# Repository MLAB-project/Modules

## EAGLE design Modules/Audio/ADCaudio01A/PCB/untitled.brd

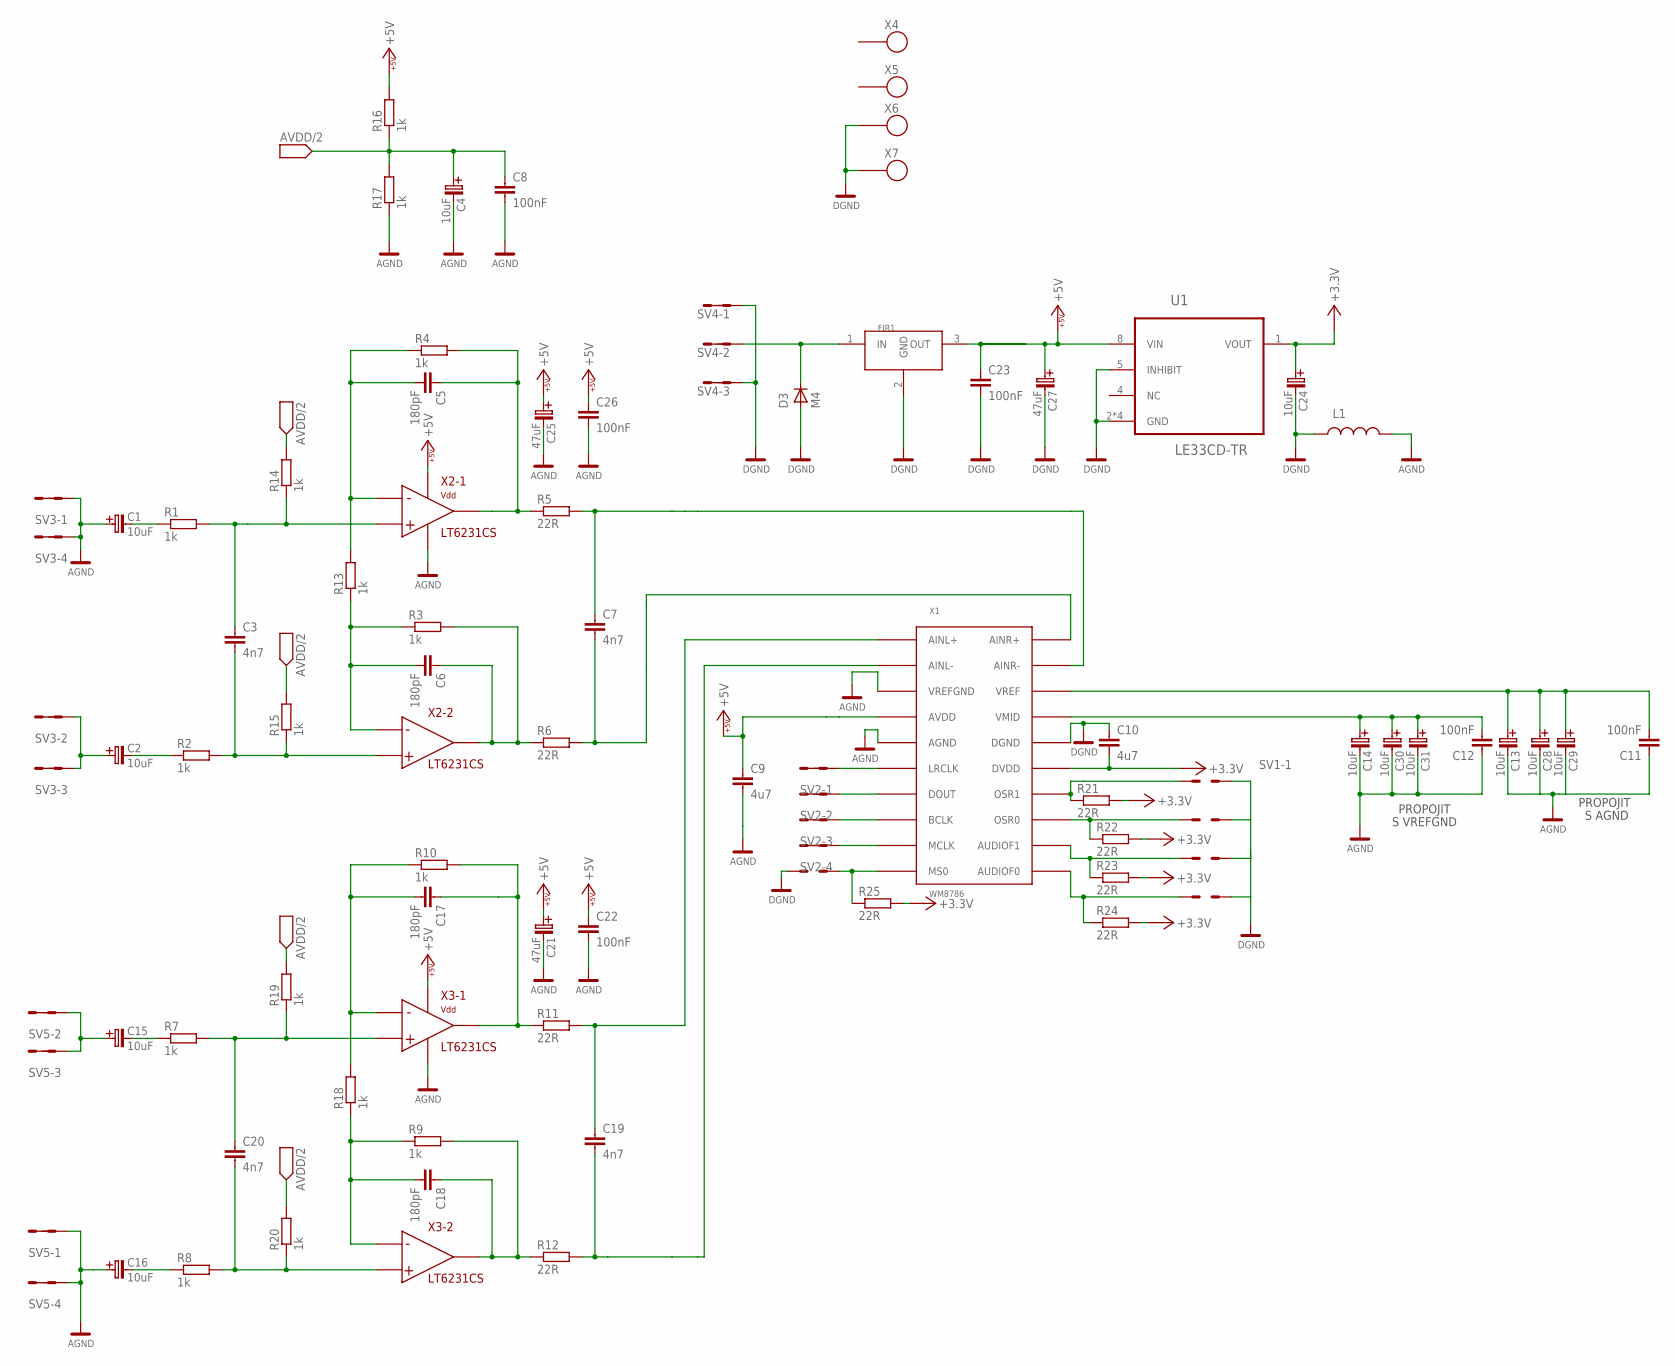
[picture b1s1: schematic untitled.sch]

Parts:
C1, C2, C4, C13, C14, C15, C16, C24, C28, C29, C30, C31: 10uF; B
C3, C7, C19, C20: 4n7; C0805
C5, C6, C17, C18: 180pF; C0805
C8, C11, C12, C22, C23, C26: 100nF; C0805
C9, C10: 4u7; C0805
C21, C25, C27: 47uF; B
D3: M4; SMA
FIR1: FILTR0805; F0805
L1: L0805
R1, R2, R3, R4, R7, R8, R9, R10, R13, R14, R15, R16, R17, R18, R19, R20: 1k; 0805
R5, R6, R11, R12, R21, R22, R23, R24, R25: 22R; 0805
SV1: MA05-3; MA05-2
SV2, SV3, SV5: MA04-2
SV4: MA03-2
U1: LE33CD-TR; SOIC127P600X175-8N
X1: WM8786; SSOP20
X2, X3: LT6231CS; SO8
X4, X5, X6, X7: SROUB3M

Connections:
1: C20.1, R7.2, R19.1, X3.3 (+)
4: C3.1, R1.2, R14.1, X2.3 (+)
+3.3V: C10.2, C24.+ (C_EL+), R21.2, R22.2, R23.2, R24.2, R25.2, U1.1 (VOUT), X1.15 (DVDD)
+5V: C9.1, C21.+ (C_EL+), C22.1, C23.1, C25.+ (C_EL+), C26.1, C27.+ (C_EL+), FIR1.3 (OUT), R16.2, U1.8 (VIN), X1.4 (AVDD), X2.8 (VDD), X3.8 (VDD)
AGND: C1.+ (C_EL+), C4.- (C_EL-), C8.2, C9.2, C11.1, C12.1, C13.- (C_EL-), C14.- (C_EL-), C16.+ (C_EL+), C21.- (C_EL-), C22.2, C25.- (C_EL-), C26.2, C28.- (C_EL-), C29.- (C_EL-), C30.- (C_EL-), C31.- (C_EL-), L1.2, R17.1, SV3.1, SV3.2, SV3.7, SV3.8, SV5.1, SV5.2, SV5.7, SV5.8, X1.3 (VREFGND), X1.5 (AGND), X2.4 (GND), X3.4 (GND)
AVDD/2: C4.+ (C_EL+), C8.1, R14.2, R15.2, R16.1, R17.2, R19.2, R20.2
DGND: C10.1, C23.2, C24.- (C_EL-), C27.- (C_EL-), D3.A, FIR1.2 (GND), L1.1, SV1.1, SV1.3, SV1.5, SV1.7, SV1.9, SV4.1, SV4.2, SV4.5, SV4.6, U1.2 (GND), U1.3 (GND), U1.5 (INHIBIT), U1.6 (GND), U1.7 (GND), X1.16 (DGND), X6.P$1, X7.P$1
unnamed: C5.2, R4.1, R13.2, X2.2 (-)
unnamed: C1.- (C_EL-), R1.1
unnamed: R21.1, SV1.8, X1.14 (OSR1)
unnamed: C6.2, R3.1, R13.1, X2.6 (-)
unnamed: C2.- (C_EL-), R2.1
unnamed: C6.1, R3.2, R6.1, X2.7 (VOUT)
unnamed: C7.1, R5.2, X1.19 (AINR-)
unnamed: R23.1, SV1.4, X1.12 (AUDIOF1)
unnamed: C17.2, R10.1, R18.2, X3.2 (-)
unnamed: C15.- (C_EL-), R7.1
unnamed: C18.2, R9.1, R18.1, X3.6 (-)
unnamed: C16.- (C_EL-), R8.1
unnamed: C18.1, R9.2, R12.1, X3.7 (VOUT)
unnamed: C19.1, R11.2, X1.1 (AINL+)
unnamed: R24.1, SV1.2, X1.11 (AUDIOF0)
unnamed: C15.+ (C_EL+), SV5.3, SV5.4, SV5.5, SV5.6
unnamed: C20.2, R8.2, R20.1, X3.5 (+)
unnamed: C2.+ (C_EL+), SV3.3, SV3.4, SV3.5, SV3.6
unnamed: R22.1, SV1.6, X1.13 (OSR0)
unnamed: C19.2, R12.2, X1.2 (AINL-)
unnamed: C12.2, C14.+ (C_EL+), C30.+ (C_EL+), C31.+ (C_EL+), X1.17 (VMID)
unnamed: C11.2, C13.+ (C_EL+), C28.+ (C_EL+), C29.+ (C_EL+), X1.18 (VREF)
unnamed: R25.1, SV1.10, X1.10 (MS0)
unnamed: SV2.1, SV2.2, X1.6 (LRCLK)
unnamed: SV2.3, SV2.4, X1.7 (DOUT)
unnamed: SV2.5, SV2.6, X1.8 (BCLK)
unnamed: SV2.7, SV2.8, X1.9 (MCLK)
unnamed: C3.2, R2.2, R15.1, X2.5 (+)
unnamed: C5.1, R4.2, R5.1, X2.1 (VOUT)
unnamed: C17.1, R10.2, R11.1, X3.1 (VOUT)
unnamed: C7.2, R6.2, X1.20 (AINR+)
unnamed: D3.K (C), FIR1.1 (IN), SV4.3, SV4.4

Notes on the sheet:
PROPOJIT
S VREFGND
S AGND

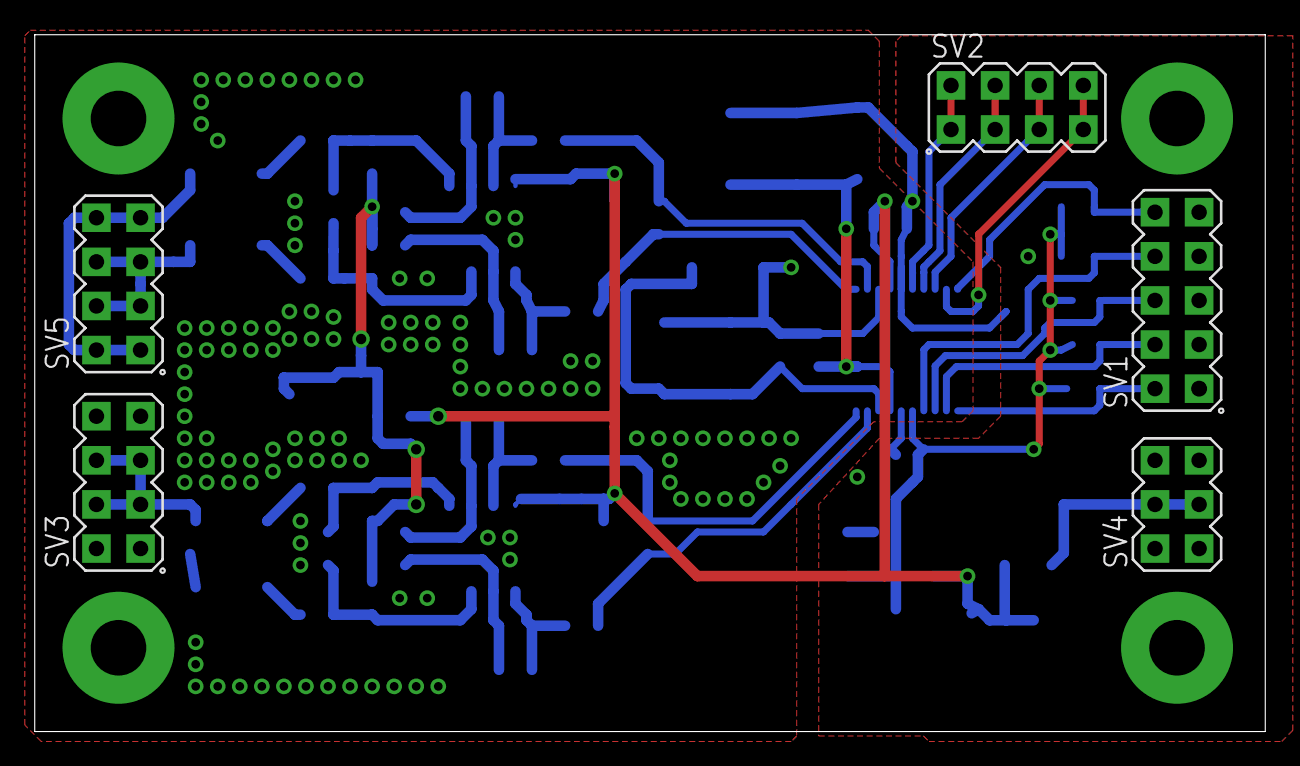
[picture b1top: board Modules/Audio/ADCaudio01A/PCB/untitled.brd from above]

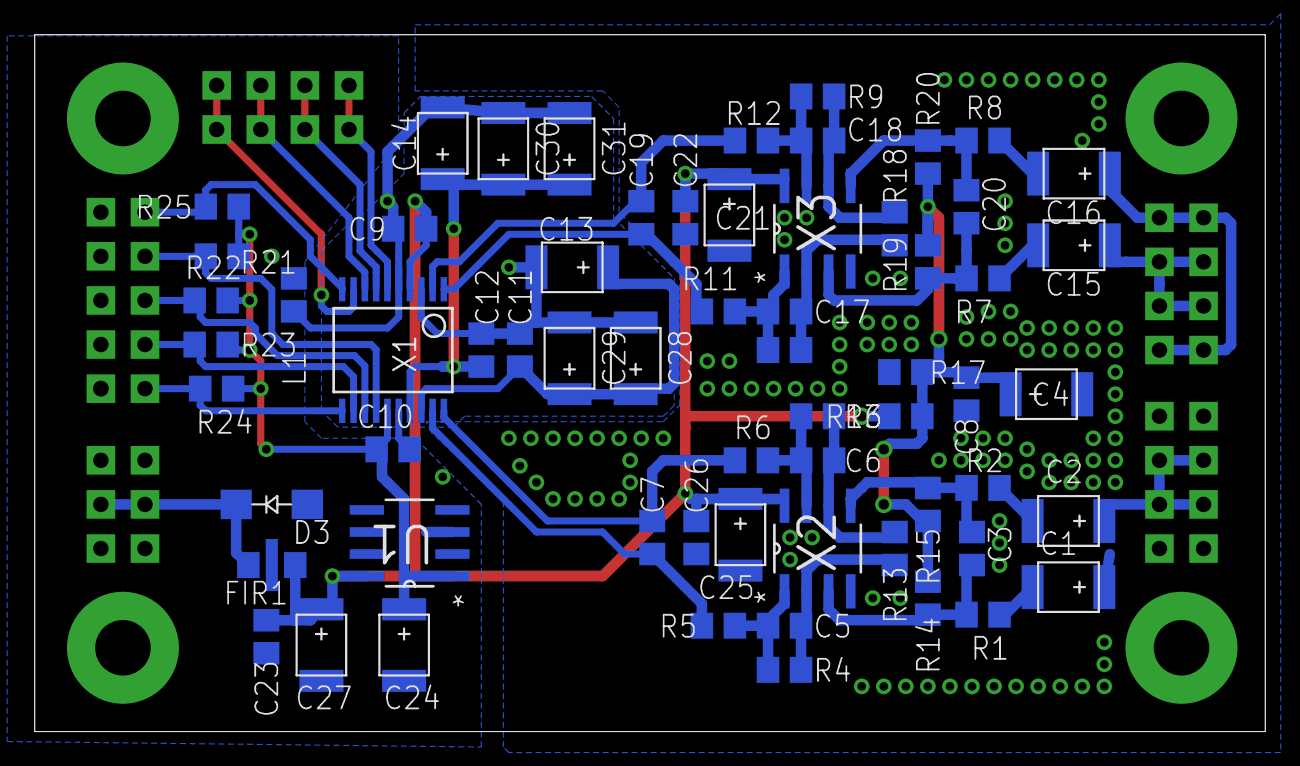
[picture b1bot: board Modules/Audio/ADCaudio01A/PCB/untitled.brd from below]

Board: 2 copper layers, 70.9 x 40.1 mm, 72 parts (63 on the bottom side), 39 nets.

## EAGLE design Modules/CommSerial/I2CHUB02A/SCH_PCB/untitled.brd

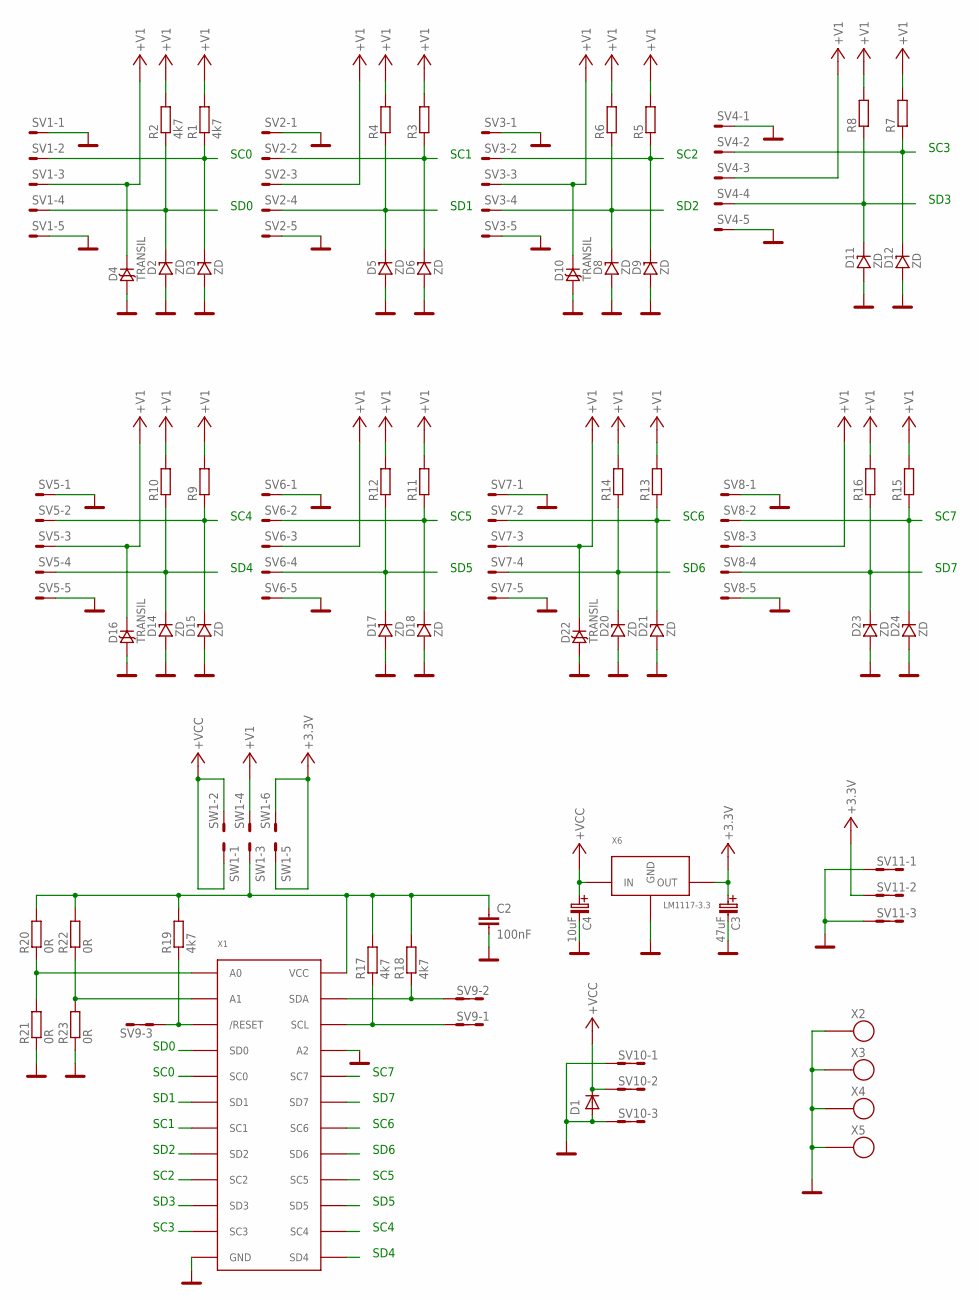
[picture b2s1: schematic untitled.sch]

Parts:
C2: 100nF; C0805
C3: 47uF; C
C4: 10uF; B
D1: D-OB.SMA; SMA
D2, D3, D5, D6, D8, D9, D11, D12, D14, D15, D17, D18, D20, D21, D23, D24: ZD; MINIMELF
D4, D10, D16, D22: TRANSIL; SMA
R1, R2, R17, R18, R19: 4k7; 0805
R3, R4, R5, R6, R7, R8, R9, R10, R11, R12, R13, R14, R15, R16: R0805; 0805
R20, R21, R22, R23: 0R; 0805
SV1, SV2, SV3, SV4, SV5, SV6, SV7, SV8: MA05-1
SV9, SV10, SV11: MA03-2
SW1: MA03-3; MA03-2
X1: TCA9548A; TSS0P24
X2, X3, X4, X5: SROUB3M
X6: LM1117-3.3; SOT223

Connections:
+3.3V: C3.+ (C_EL+), SV11.3, SV11.4, SW1.5, SW1.6, X6.2 (OUT), X6.4 (OUT)
+V1: D4.K, D10.K, D16.K, D22.K, R1.2, R2.2, R3.2, R4.2, R5.2, R6.2, R7.2, R8.2, R9.2, R10.2, R11.2, R12.2, R13.2, R14.2, R15.2, R16.2, SV1.3, SV2.3, SV3.3, SV4.3, SV5.3, SV6.3, SV7.3, SV8.3, SW1.4
+VCC: C4.+ (C_EL+), D1.K (C), SV10.3, SV10.4, SW1.1, SW1.2, X6.3 (IN)
/RESET: R19.1, SV9.5, SV9.6, X1.3 (/RESET)
GND: C2.2, C3.- (C_EL-), C4.- (C_EL-), D1.A, D2.A, D3.A, D4.A, D5.A, D6.A, D8.A, D9.A, D10.A, D11.A, D12.A, D14.A, D15.A, D16.A, D17.A, D18.A, D20.A, D21.A, D22.A, D23.A, D24.A, R21.1, R23.1, SV1.1, SV1.5, SV2.1, SV2.5, SV3.1, SV3.5, SV4.1, SV4.5, SV5.1, SV5.5, SV6.1, SV6.5, SV7.1, SV7.5, SV8.1, SV8.5, SV10.1, SV10.2, SV10.5, SV10.6, SV11.1, SV11.2, SV11.5, SV11.6, X1.12 (GND), X1.21 (A2), X2.P$1, X3.P$1, X4.P$1, X5.P$1, X6.1 (GND)
unnamed: C2.1, R17.2, R18.2, R19.2, R20.2, R22.2, SW1.3, X1.24 (VCC)
unnamed: R20.1, R21.2, X1.1 (A0)
unnamed: R22.1, R23.2, X1.2 (A1)
SC0: D3.C (K), R1.1, SV1.2, X1.5 (SC0)
SC1: D6.C (K), R3.1, SV2.2, X1.7 (SC1)
SC2: D9.C (K), R5.1, SV3.2, X1.9 (SC2)
SC3: D12.C (K), R7.1, SV4.2, X1.11 (SC3)
SC4: D15.C (K), R9.1, SV5.2, X1.14 (SC4)
SC5: D18.C (K), R11.1, SV6.2, X1.16 (SC5)
SC6: D21.C (K), R13.1, SV7.2, X1.18 (SC6)
SC7: D24.C (K), R15.1, SV8.2, X1.20 (SC7)
SCL: R17.1, SV9.1, SV9.2, X1.22 (SCL)
SD0: D2.C (K), R2.1, SV1.4, X1.4 (SD0)
SD1: D5.C (K), R4.1, SV2.4, X1.6 (SD1)
SD2: D8.C (K), R6.1, SV3.4, X1.8 (SD2)
SD3: D11.C (K), R8.1, SV4.4, X1.10 (SD3)
SD4: D14.C (K), R10.1, SV5.4, X1.13 (SD4)
SD5: D17.C (K), R12.1, SV6.4, X1.15 (SD5)
SD6: D20.C (K), R14.1, SV7.4, X1.17 (SD6)
SD7: D23.C (K), R16.1, SV8.4, X1.19 (SD7)
SDA: R18.1, SV9.3, SV9.4, X1.23 (SDA)

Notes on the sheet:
SC0
SD0
SC1
SD1
SC2
SD2
SC3
SD3
SC4
SD4
SC5
SD5
SC6
SD6
SC7
SD7

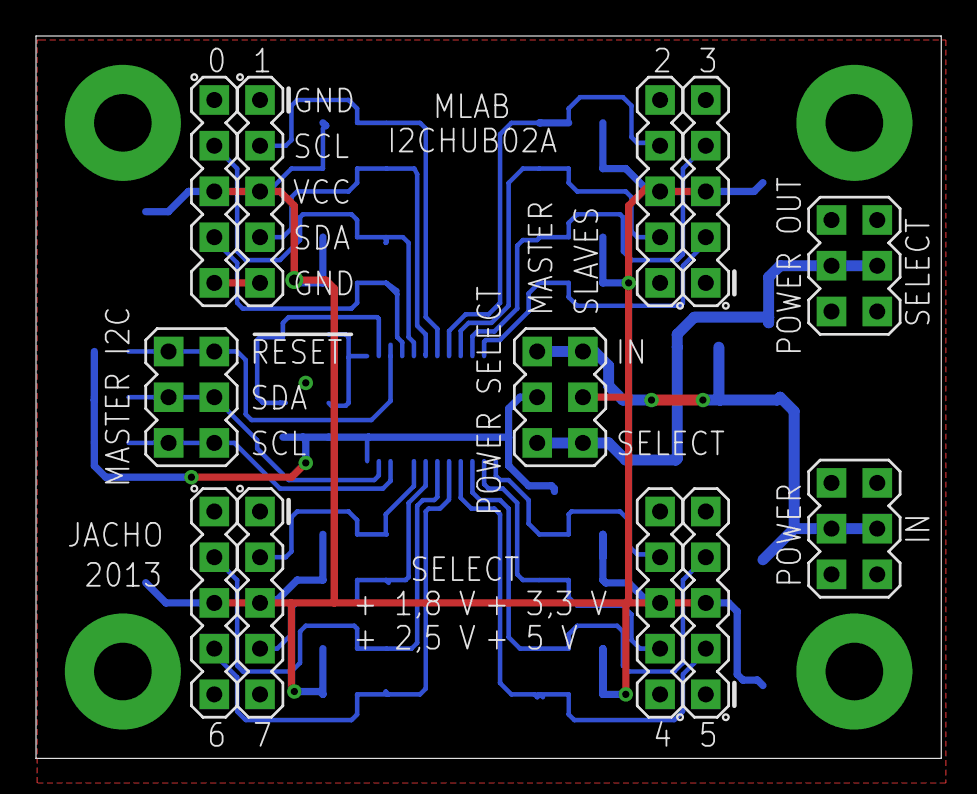
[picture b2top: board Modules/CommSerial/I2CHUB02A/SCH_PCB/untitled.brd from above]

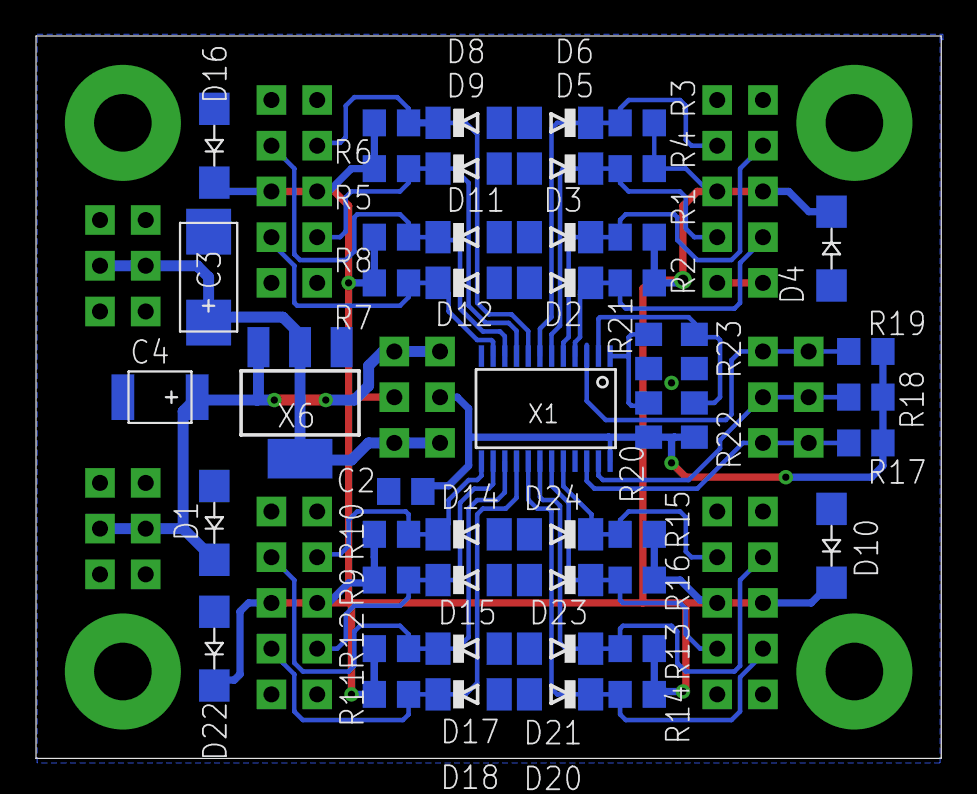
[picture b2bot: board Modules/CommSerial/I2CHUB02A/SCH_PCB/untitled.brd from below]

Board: 2 copper layers, 50.3 x 40.1 mm, 65 parts (49 on the bottom side), 26 nets.

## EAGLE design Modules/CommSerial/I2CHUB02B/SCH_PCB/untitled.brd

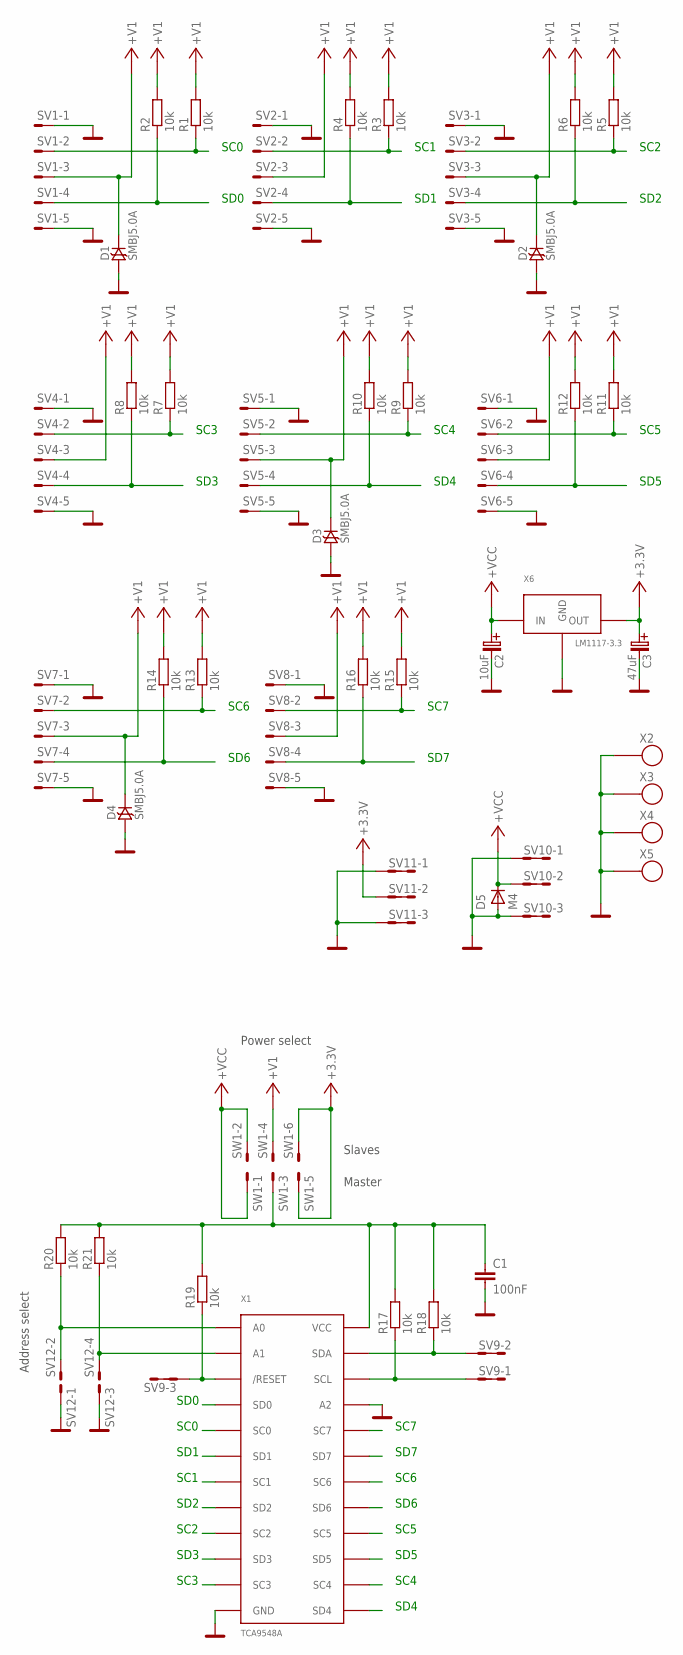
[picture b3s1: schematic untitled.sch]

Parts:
C1: 100nF; C0805
C2: 10uF; B
C3: 47uF; C
D1, D2, D3, D4: SMBJ5.0A; SMA
D5: M4; SMA
R1, R2, R3, R4, R5, R6, R7, R8, R9, R10, R11, R12, R13, R14, R15, R16, R17, R18, R19, R20, R21: 10k; 0805
SV1, SV2, SV3, SV4, SV5, SV6, SV7, SV8: MA05-1
SV9, SV10, SV11: MA03-2
SV12: MA02-3; MA02-2
SW1: MA03-3; MA03-2
X1: TCA9548A; TSS0P24
X2, X3, X4, X5: SROUB3M
X6: LM1117-3.3; SOT223

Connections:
+3.3V: C3.+ (C_EL+), SV11.3, SV11.4, SW1.5, SW1.6, X6.2 (OUT), X6.4 (OUT)
+V1: D1.K, D2.K, D3.K, D4.K, R1.2, R2.2, R3.2, R4.2, R5.2, R6.2, R7.2, R8.2, R9.2, R10.2, R11.2, R12.2, R13.2, R14.2, R15.2, R16.2, SV1.3, SV2.3, SV3.3, SV4.3, SV5.3, SV6.3, SV7.3, SV8.3, SW1.4
+VCC: C2.+ (C_EL+), D5.K (C), SV10.3, SV10.4, SW1.1, SW1.2, X6.3 (IN)
/RESET: R19.1, SV9.5, SV9.6, X1.3 (/RESET)
A0: R20.1, SV12.2, X1.1 (A0)
GND: C1.2, C2.- (C_EL-), C3.- (C_EL-), D1.A, D2.A, D3.A, D4.A, D5.A, SV1.1, SV1.5, SV2.1, SV2.5, SV3.1, SV3.5, SV4.1, SV4.5, SV5.1, SV5.5, SV6.1, SV6.5, SV7.1, SV7.5, SV8.1, SV8.5, SV10.1, SV10.2, SV10.5, SV10.6, SV11.1, SV11.2, SV11.5, SV11.6, SV12.1, SV12.3, X1.12 (GND), X1.21 (A2), X2.P$1, X3.P$1, X4.P$1, X5.P$1, X6.1 (GND)
unnamed: R21.1, SV12.4, X1.2 (A1)
unnamed: C1.1, R17.2, R18.2, R19.2, R20.2, R21.2, SW1.3, X1.24 (VCC)
SC0: R1.1, SV1.2, X1.5 (SC0)
SC1: R3.1, SV2.2, X1.7 (SC1)
SC2: R5.1, SV3.2, X1.9 (SC2)
SC3: R7.1, SV4.2, X1.11 (SC3)
SC4: R9.1, SV5.2, X1.14 (SC4)
SC5: R11.1, SV6.2, X1.16 (SC5)
SC6: R13.1, SV7.2, X1.18 (SC6)
SC7: R15.1, SV8.2, X1.20 (SC7)
SCL: R17.1, SV9.1, SV9.2, X1.22 (SCL)
SD0: R2.1, SV1.4, X1.4 (SD0)
SD1: R4.1, SV2.4, X1.6 (SD1)
SD2: R6.1, SV3.4, X1.8 (SD2)
SD3: R8.1, SV4.4, X1.10 (SD3)
SD4: R10.1, SV5.4, X1.13 (SD4)
SD5: R12.1, SV6.4, X1.15 (SD5)
SD6: R14.1, SV7.4, X1.17 (SD6)
SD7: R16.1, SV8.4, X1.19 (SD7)
SDA: R18.1, SV9.3, SV9.4, X1.23 (SDA)

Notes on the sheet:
SC0
SD0
SC1
SD1
SC2
SD2
SC3
SD3
SC4
SD4
SC5
SD5
SC6
SD6
SC7
SD7
Power select
Master
Slaves
Address select

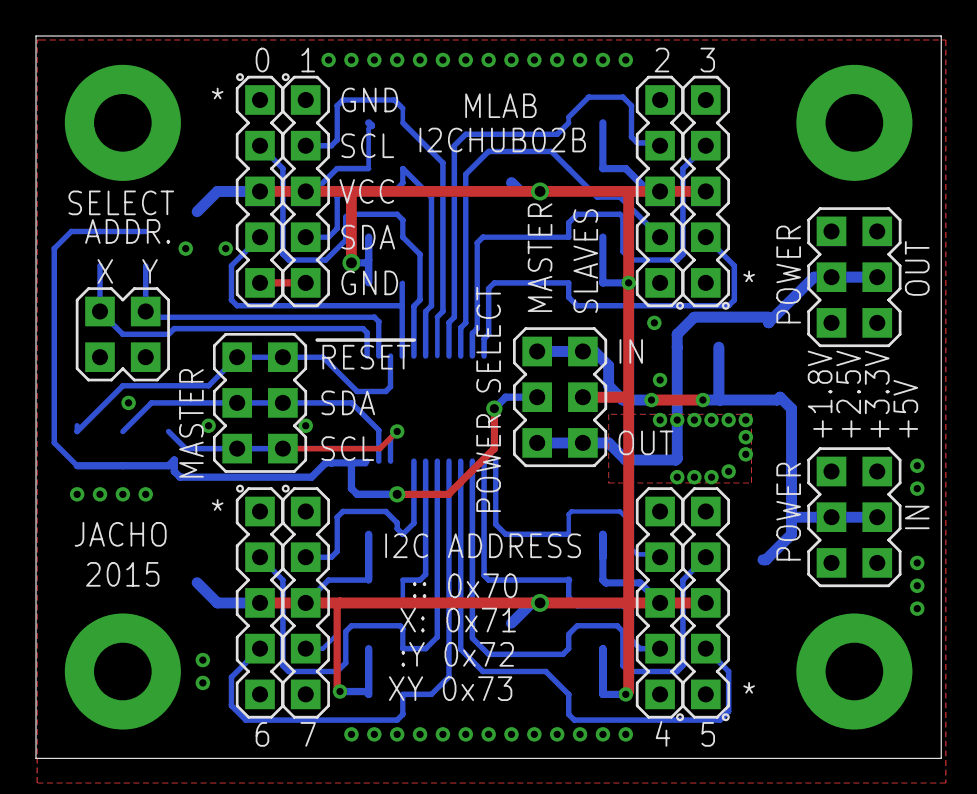
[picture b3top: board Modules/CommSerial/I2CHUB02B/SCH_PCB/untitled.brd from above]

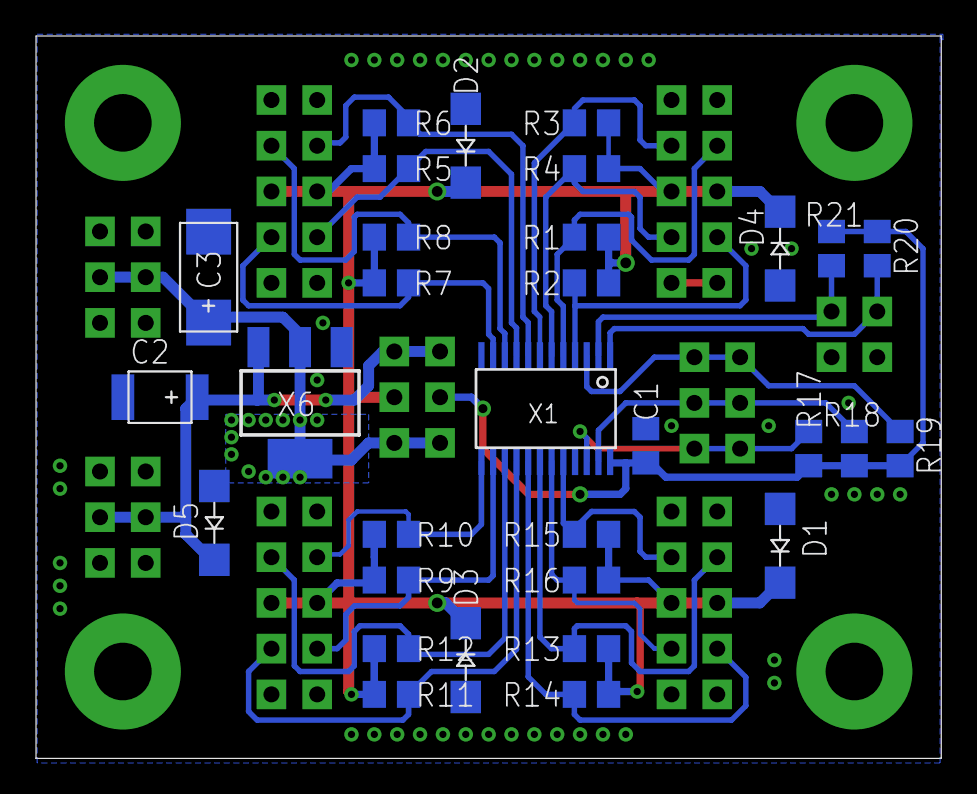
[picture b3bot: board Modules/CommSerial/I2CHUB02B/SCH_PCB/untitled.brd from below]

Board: 2 copper layers, 50.3 x 40.1 mm, 48 parts (31 on the bottom side), 26 nets.

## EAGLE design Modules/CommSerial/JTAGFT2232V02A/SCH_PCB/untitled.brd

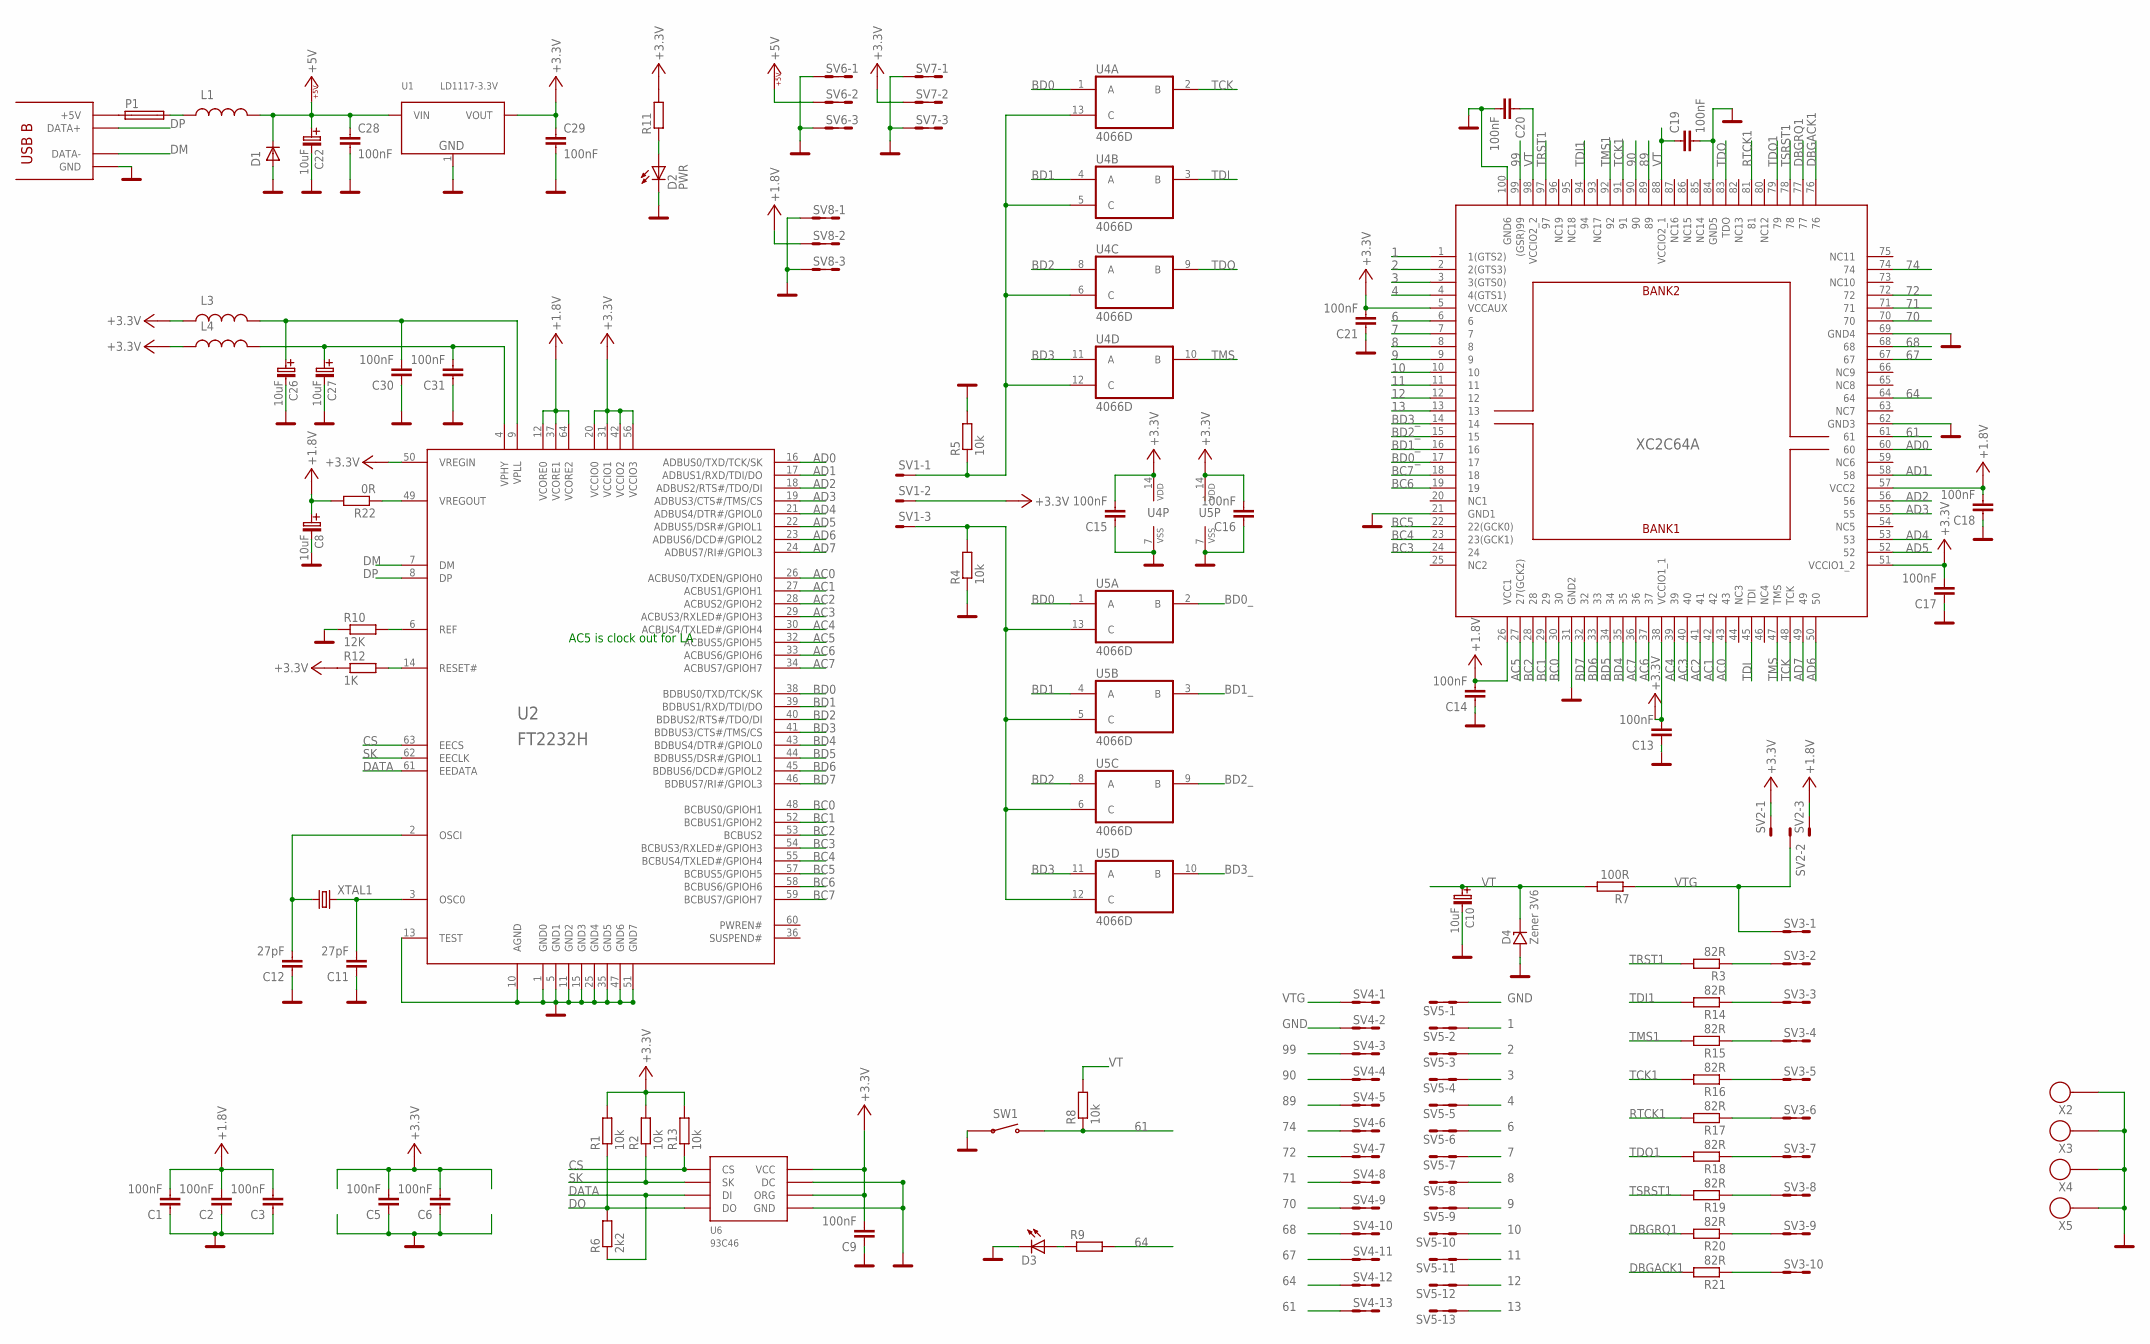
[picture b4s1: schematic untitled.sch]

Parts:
C1, C2, C3, C5, C6, C9, C13, C14, C15, C16, C17, C18, C19, C20, C21, C28, C29, C30, C31: 100nF; C0805
C8, C10, C22, C26, C27: 10uF; B
C11, C12: 27pF; C0805
D1: D-OB.SMA; SMA
D2: PWR; 1206
D3: LED1206; 1206
D4: Zener 3V6; MINIMELF
L1: L0805
L3, L4: L1210; 1210
P1: POJISTKA_1812; 1812
R1, R2, R4, R5, R8, R13: 10k; 0805
R3, R14, R15, R16, R17, R18, R19, R20, R21: 82R; 0805
R6: 2k2; 0805
R7: 100R; 0805
R9, R11: R0805; 0805
R10: 12K; 0805
R12: 1K; 0805
R22: 0R; 0805
SV1, SV2: MA03-1
SV3: MA10-2
SV4, SV5: MA13-2
SV6, SV7, SV8: MA03-2
SW1: TACT-64K
U1: LD1117-3.3V; SOT223
U2: FT2232H; LQFP64
U3: XC2C64A; VQ100
U4, U5: 4066D; SO14
U6: 93C46; SOIC8
X1: USB_B
X2, X3, X4, X5: SROUB3M
XTAL1: KRYSLAL_S49; S49

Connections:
1: SV5.3, SV5.4, U3.1 (1(GTS2))
2: SV5.5, SV5.6, U3.2 (2(GTS3))
3: SV5.7, SV5.8, U3.3 (3(GTS0))
4: SV5.9, SV5.10, U3.4 (4(GTS1))
6: SV5.11, SV5.12, U3.6
7: SV5.13, SV5.14, U3.7
8: SV5.15, SV5.16, U3.8
9: SV5.17, SV5.18, U3.9
10: SV5.19, SV5.20, U3.10
11: SV5.21, SV5.22, U3.11
12: SV5.23, SV5.24, U3.12
13: SV5.25, SV5.26, U3.13
61: R8.1, SV4.25, SV4.26, SW1.P$3, SW1.P$4, U3.61
64: R9.2, SV4.23, SV4.24, U3.64
67: SV4.21, SV4.22, U3.67
68: SV4.19, SV4.20, U3.68
70: SV4.17, SV4.18, U3.70
71: SV4.15, SV4.16, U3.71
72: SV4.13, SV4.14, U3.72
74: SV4.11, SV4.12, U3.74
89: SV4.9, SV4.10, U3.89
90: SV4.7, SV4.8, U3.90
99: SV4.5, SV4.6, U3.99 ((GSR)99)
+3.3V: C5.2, C6.2, C9.2, C13.2, C15.2, C16.2, C17.2, C21.2, C29.1, L3.P$1 (1), L4.P$1 (1), R1.2, R2.2, R11.2, R12.1, R13.2, SV1.2, SV2.1, SV7.3, SV7.4, U1.2 (VOUT), U2.20 (VCCIO0), U2.31 (VCCIO1), U2.42 (VCCIO2), U2.50 (VREGIN), U2.56 (VCCIO3), U3.5 (VCCAUX), U3.38 (VCCIO1_1), U3.51 (VCCIO1_2), U4.14 (VDD), U5.14 (VDD), U6.6 (ORG), U6.8 (VCC)
+5V: C22.+ (C_EL+), C28.1, D1.K (C), L1.2, SV6.3, SV6.4, U1.3 (VIN)
AC0: U2.26 (ACBUS0/TXDEN/GPIOH0), U3.43
AC1: U2.27 (ACBUS1/GPIOH1), U3.42
AC2: U2.28 (ACBUS2/GPIOH2), U3.41
AC3: U2.29 (ACBUS3/RXLED#/GPIOH3), U3.40
AC4: U2.30 (ACBUS4/TXLED#/GPIOH4), U3.39
AC5: U2.32 (ACBUS5/GPIOH5), U3.27 (27(GCK2))
AC6: U2.33 (ACBUS6/GPIOH6), U3.37
AC7: U2.34 (ACBUS7/GPIOH7), U3.36
AD0: U2.16 (ADBUS0/TXD/TCK/SK), U3.60
AD1: U2.17 (ADBUS1/RXD/TDI/DO), U3.58
AD2: U2.18 (ADBUS2/RTS#/TDO/DI), U3.56
AD3: U2.19 (ADBUS3/CTS#/TMS/CS), U3.55
AD4: U2.21 (ADBUS4/DTR#/GPIOL0), U3.53
AD5: U2.22 (ADBUS5/DSR#/GPIOL1), U3.52
AD6: U2.23 (ADBUS6/DCD#/GPIOL2), U3.50
AD7: U2.24 (ADBUS7/RI#/GPIOL3), U3.49
BC0: U2.48 (BCBUS0/GPIOH1), U3.30
BC1: U2.52 (BCBUS1/GPIOH2), U3.29
BC2: U2.53 (BCBUS2), U3.28
BC3: U2.54 (BCBUS3/RXLED#/GPIOH3), U3.24
BC4: U2.55 (BCBUS4/TXLED#/GPIOH4), U3.23 (23(GCK1))
BC5: U2.57 (BCBUS5/GPIOH5), U3.22 (22(GCK0))
BC6: U2.58 (BCBUS6/GPIOH6), U3.19
BC7: U2.59 (BCBUS7/GPIOH7), U3.18
BD0: U2.38 (BDBUS0/TXD/TCK/SK), U4.1 (A), U5.1 (A)
BD0_: U3.17, U5.2 (B)
BD1: U2.39 (BDBUS1/RXD/TDI/DO), U4.4 (A), U5.4 (A)
BD1_: U3.16, U5.3 (B)
BD2: U2.40 (BDBUS2/RTS#/TDO/DI), U4.8 (A), U5.8 (A)
BD2_: U3.15, U5.9 (B)
BD3: U2.41 (BDBUS3/CTS#/TMS/CS), U4.11 (A), U5.11 (A)
BD3_: U3.14, U5.10 (B)
BD4: U2.43 (BDBUS4/DTR#/GPIOL0), U3.35
BD5: U2.44 (BDBUS5/DSR#/GPIOL1), U3.34
BD6: U2.45 (BDBUS6/DCD#/GPIOL2), U3.33
BD7: U2.46 (BDBUS7/RI#/GPIOL3), U3.32
CS: R13.1, U2.63 (EECS), U6.1 (CS)
DATA: R6.1, U2.61 (EEDATA), U6.3 (DI)
DBGACK1: R21.2, U3.76
DBGRQ1: R20.2, U3.77
DM: U2.7 (DM), X1.2 (DATA-)
DO: R1.1, R6.2, U6.4 (DO)
DP: U2.8 (DP), X1.3 (DATA+)
GND: C1.1, C2.1, C3.1, C5.1, C6.1, C8.- (C_EL-), C9.1, C10.- (C_EL-), C11.1, C12.1, C13.1, C14.1, C15.1, C16.1, C17.1, C18.1, C19.2, C20.2, C21.1, C22.- (C_EL-), C26.- (C_EL-), C27.- (C_EL-), C28.2, C29.2, C30.1, C31.1, D1.A, D2.K (C), D3.K (C), D4.A, R4.1, R5.2, R10.1, SV4.3, SV4.4, SV5.1, SV5.2, SV6.1, SV6.2, SV6.5, SV6.6, SV7.1, SV7.2, SV7.5, SV7.6, SV8.1, SV8.2, SV8.5, SV8.6, SW1.P$1, SW1.P$2, U1.1 (GND), U2.1 (GND0), U2.5 (GND1), U2.10 (AGND), U2.11 (GND2), U2.13 (TEST), U2.15 (GND3), U2.25 (GND4), U2.35 (GND5), U2.47 (GND6), U2.51 (GND7), U3.21 (GND1), U3.31 (GND2), U3.62 (GND3), U3.69 (GND4), U3.84 (GND5), U3.100 (GND6), U4.7 (VSS), U5.7 (VSS), U6.5 (GND), U6.7 (DC), X1.4 (GND), X1.GND, X1.GND2 (GND), X2.P$1, X3.P$1, X4.P$1, X5.P$1
unnamed: C11.2, U2.3 (OSC0), XTAL1.P$2 (2)
unnamed: C12.2, U2.2 (OSCI), XTAL1.P$1 (1)
unnamed: R10.2, U2.6 (REF)
unnamed: R12.2, U2.14 (RESET#)
unnamed: R3.1, SV3.3, SV3.4
unnamed: D3.A, R9.1
unnamed: D2.A, R11.1
unnamed: P1.1, X1.1 (+5V)
unnamed: L1.1, P1.2
unnamed: R14.1, SV3.5, SV3.6
unnamed: R15.1, SV3.7, SV3.8
unnamed: R16.1, SV3.9, SV3.10
unnamed: R17.1, SV3.11, SV3.12
unnamed: R18.1, SV3.13, SV3.14
unnamed: R19.1, SV3.15, SV3.16
unnamed: R20.1, SV3.17, SV3.18
unnamed: R21.1, SV3.19, SV3.20
unnamed: R22.1, U2.49 (VREGOUT)
unnamed: R5.1, SV1.1, U4.5 (C), U4.6 (C), U4.12 (C), U4.13 (C)
unnamed: R4.2, SV1.3, U5.5 (C), U5.6 (C), U5.12 (C), U5.13 (C)
RTCK1: R17.2, U3.81
SK: R2.1, U2.62 (EECLK), U6.2 (SK)
TCK: U3.48 (TCK), U4.2 (B)
TCK1: R16.2, U3.91
TDI: U3.45 (TDI), U4.3 (B)
TDI1: R14.2, U3.94
TDO: U3.83 (TDO), U4.9 (B)
TDO1: R18.2, U3.79
TMS: U3.47 (TMS), U4.10 (B)
TMS1: R15.2, U3.92
TRST1: R3.2, U3.97
TSRST1: R19.2, U3.78
VPHY: C27.+ (C_EL+), C31.2, L4.P$2 (2), U2.4 (VPHY)
VPLL: C26.+ (C_EL+), C30.2, L3.P$2 (2), U2.9 (VPLL)
VT: C10.+ (C_EL+), C19.1, C20.1, D4.C (K), R7.2, R8.2, U3.88 (VCCIO2_1), U3.98 (VCCIO2_2)

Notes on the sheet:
AC5 is clock out for LA
XC2C64A

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

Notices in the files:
parts and their libraries:
PaJa_C-tantal_SMD: Copyright (C) PaJa 2009
PaJa_22: Copyright (C) PaJa 2001-2010
